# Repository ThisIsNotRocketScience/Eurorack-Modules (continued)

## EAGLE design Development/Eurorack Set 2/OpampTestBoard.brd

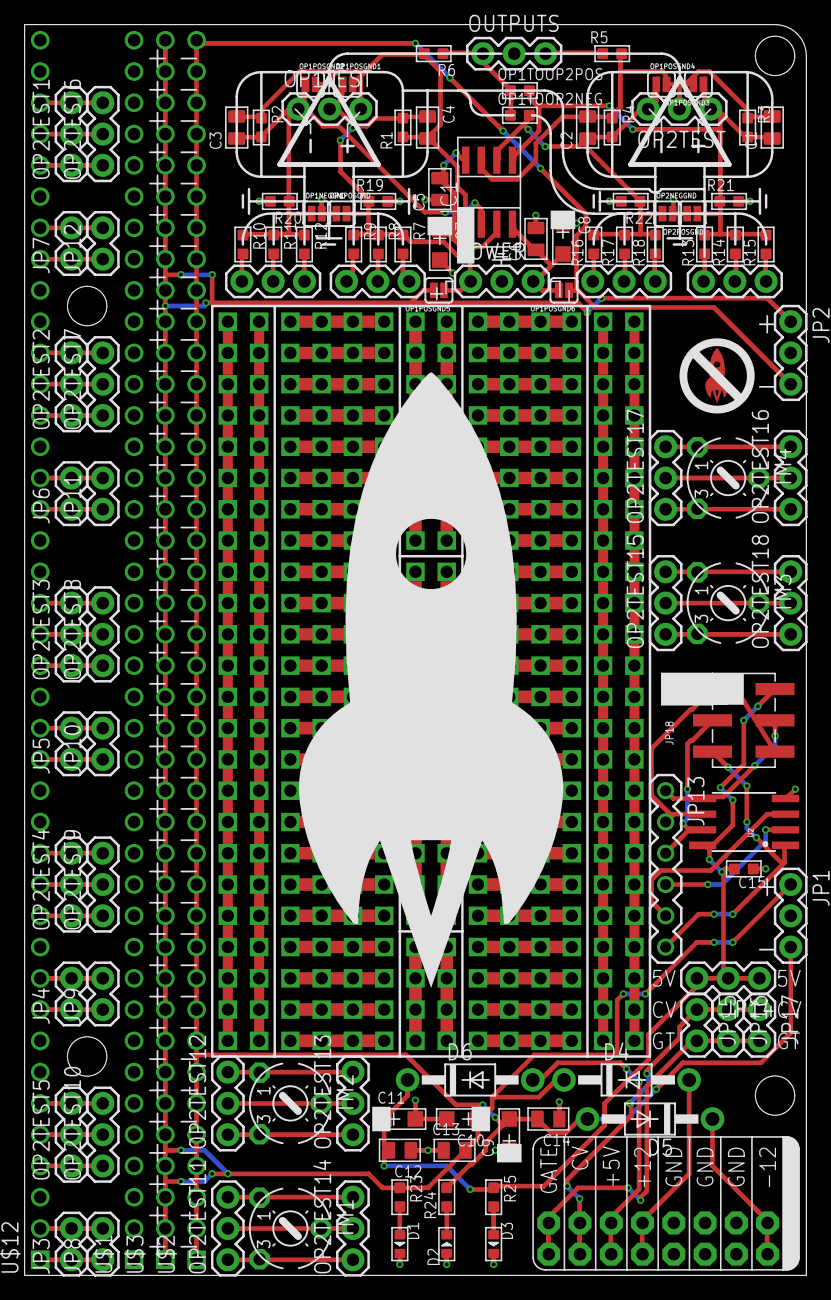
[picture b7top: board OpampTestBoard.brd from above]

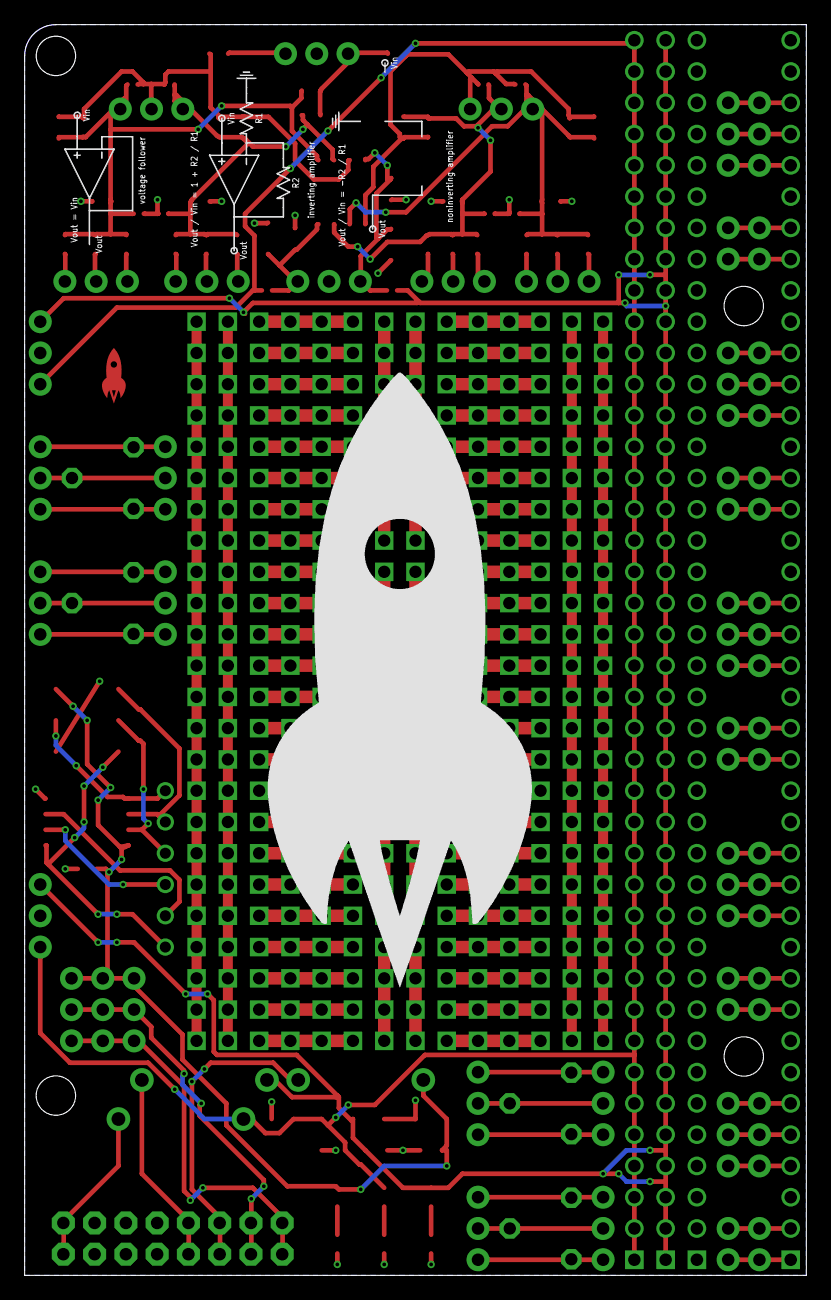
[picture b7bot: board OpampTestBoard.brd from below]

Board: 2 copper layers, 63.5 x 101.6 mm, 125 parts (5 on the bottom side), 77 nets.

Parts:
C1, C2, C3, C4, C5, C6, C12, C13, C14: C0805
C7, C8, C9, C10, C11: AVX-A
C15: C0603
D1, D2, D3: LED0603
D4, D5, D6: DO41-10
H1, H2, H3, H4: MOUNT-HOLE; 3.2-NOMARKINGS-SMALLSAFEZONE
IC1: TL072; SO08
JP1, JP2, JP14: 1X03
JP3, JP4, JP5, JP6, JP7, JP8, JP9, JP10, JP11, JP12, JP15, JP16, JP17: M02PTH; 1X02
JP13: 1X06
JP18: 2X3_SMT_POSTS
OP1NEG, OP1POS, OP1TEST, OP2NEG, OP2POS, OP2TEST, OP2TEST1, OP2TEST2, OP2TEST3, OP2TEST4, OP2TEST5, OP2TEST6, OP2TEST7, OP2TEST8, OP2TEST9, OP2TEST10, OP2TEST11, OP2TEST12, OP2TEST13, OP2TEST14, OP2TEST15, OP2TEST16, OP2TEST17, OP2TEST18: 1X03
OP1NEGGND, OP1POSGND, OP1POSGND1, OP1POSGND2, OP1POSGND3, OP1POSGND4, OP1POSGND5, OP1POSGND6, OP2NEGGND, OP2POSGND: SOLDERJUMPERNC; SJ_2S
OP1TOOP2NEG, OP1TOOP2POS: R0603
OUTPUTS: 1X03
POWER: 1X03
R1, R2, R3, R4, R5, R6, R7, R8, R9, R10, R11, R12, R13, R14, R15, R16, R17, R18, R19, R20, R21, R22, R23, R24, R25: R0603
TM1, TM2, TM3, TM4: 6MM
U2: Tiny85-20-SMT; SO08-EIAJ
U$1, U$2, U$3, U$12: M40; 1X40
U$4, U$7: SYMBOLSOPAMP; SYMB_OPAMP
U$5: R2; RESISTOR
U$6: R1; RESISTOR
U$8: SMALLROCKET
U$9: POWER; POWER_16
U$10, U$17: ROCKET-5CM
U$32: PROTOAREA; PROTO_10_24

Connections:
1: JP13.2, JP18.1, U2.6
2: JP13.3, JP18.3, U2.7
3: JP13.4, U2.2
4: JP13.5, U2.3
+5V: C11.+, C12.2, C15.2, D6.C, JP14.1, JP14.2, JP14.3, JP18.2, R25.1, U2.8
+12V: C10.+, C13.2, D4.C, JP1.1, JP2.1, OP1POSGND5.2, R23.1, U$3.1, U$3.2, U$3.3, U$3.4, U$3.5, U$3.6, U$3.7, U$3.8, U$3.9, U$3.10, U$3.11, U$3.12, U$3.13, U$3.14, U$3.15, U$3.16, U$3.17, U$3.18, U$3.19, U$3.20, U$3.21, U$3.22, U$3.23, U$3.24, U$3.25, U$3.26, U$3.27, U$3.28, U$3.29, U$3.30, U$3.31, U$3.32, U$3.33, U$3.34, U$3.35, U$3.36, U$3.37, U$3.38, U$3.39, U$3.40
-12V: C9.-, C14.2, D5.A, JP1.3, JP2.3, OP1POSGND6.1, R24.2, U$2.1, U$2.2, U$2.3, U$2.4, U$2.5, U$2.6, U$2.7, U$2.8, U$2.9, U$2.10, U$2.11, U$2.12, U$2.13, U$2.14, U$2.15, U$2.16, U$2.17, U$2.18, U$2.19, U$2.20, U$2.21, U$2.22, U$2.23, U$2.24, U$2.25, U$2.26, U$2.27, U$2.28, U$2.29, U$2.30, U$2.31, U$2.32, U$2.33, U$2.34, U$2.35, U$2.36, U$2.37, U$2.38, U$2.39, U$2.40
A1: OP2TEST1.3, OP2TEST6.3, U$12.38
A2: OP2TEST1.2, OP2TEST6.2, U$12.37
A3: OP2TEST1.1, OP2TEST6.1, U$12.36
B1: OP2TEST2.3, OP2TEST7.3, U$12.30
B2: OP2TEST2.2, OP2TEST7.2, U$12.29
B3: OP2TEST2.1, OP2TEST7.1, U$12.28
C1: OP2TEST3.3, OP2TEST8.3, U$12.22
C2: OP2TEST3.2, OP2TEST8.2, U$12.21
C3: OP2TEST3.1, OP2TEST8.1, U$12.20
CV: JP15.1, JP16.1, JP17.1, U$9.13, U$9.14
D1: OP2TEST4.3, OP2TEST9.3, U$12.14
D2: OP2TEST4.2, OP2TEST9.2, U$12.13
D3: OP2TEST4.1, OP2TEST9.1, U$12.12
E1: OP2TEST5.3, OP2TEST10.3, U$12.6
E2: OP2TEST5.2, OP2TEST10.2, U$12.5
E3: OP2TEST5.1, OP2TEST10.1, U$12.4
GATE: JP15.2, JP16.2, JP17.2, U$9.15, U$9.16
GND: C5.1, C6.2, C7.-, C8.+, C9.+, C10.-, C11.-, C12.1, C13.1, C14.1, C15.1, D1.-, D2.+, D3.-, JP1.2, JP2.2, JP18.6, OP1NEGGND.2, OP1POSGND.1, OP2NEGGND.2, OP2POSGND.2, OUTPUTS.2, POWER.2, R19.2, R20.2, R21.2, R22.2, U2.4, U$1.1, U$1.2, U$1.3, U$1.4, U$1.5, U$1.6, U$1.7, U$1.8, U$1.9, U$1.10, U$1.11, U$1.12, U$1.13, U$1.14, U$1.15, U$1.16, U$1.17, U$1.18, U$1.19, U$1.20, U$1.21, U$1.22, U$1.23, U$1.24, U$1.25, U$1.26, U$1.27, U$1.28, U$1.29, U$1.30, U$1.31, U$1.32, U$1.33, U$1.34, U$1.35, U$1.36, U$1.37, U$1.38, U$1.39, U$1.40, U$9.3, U$9.4, U$9.5, U$9.6, U$9.7, U$9.8, U$12.3, U$12.7, U$12.8, U$12.11, U$12.15, U$12.16, U$12.19, U$12.23, U$12.24, U$12.27, U$12.31, U$12.32, U$12.35, U$12.39, U$12.40
LA1: JP7.1, JP12.1, U$12.33
LA2: JP7.2, JP12.2, U$12.34
LB1: JP6.1, JP11.1, U$12.25
LB2: JP6.2, JP11.2, U$12.26
LC1: JP5.1, JP10.1, U$12.17
LC2: JP5.2, JP10.2, U$12.18
LD1: JP4.1, JP9.1, U$12.9
LD2: JP4.2, JP9.2, U$12.10
LE1: JP3.1, JP8.1, U$12.1
LE2: JP3.2, JP8.2, U$12.2
MOSI: JP13.1, JP18.4, U2.5
unnamed: OP1POS.3, R9.2
unnamed: OP1TOOP2NEG.1, OP1TOOP2POS.1, OUTPUTS.1, R6.1
unnamed: OP1POS.2, R8.2
unnamed: OUTPUTS.3, R5.1
unnamed: OP2TEST11.2, OP2TEST14.2, TM1.S
unnamed: OP2TEST12.2, OP2TEST13.2, TM2.S
unnamed: OP1POS.1, R7.2
unnamed: OP1NEG.3, R10.2
unnamed: OP1NEG.2, R11.2
unnamed: OP1NEG.1, R12.2
unnamed: OP2POS.3, R13.1
unnamed: OP2POS.2, R14.1
unnamed: OP2POS.1, R15.1
unnamed: OP2NEG.3, R16.1
unnamed: OP2NEG.2, R17.1
unnamed: OP2NEG.1, R18.1
unnamed: OP2TEST12.1, OP2TEST13.1, TM2.E
unnamed: D3.+, R25.2
unnamed: D1.+, R23.2
unnamed: D2.-, R24.1
unnamed: OP2TEST12.3, OP2TEST13.3, TM2.A
unnamed: OP2TEST11.1, OP2TEST14.1, TM1.E
unnamed: OP2TEST11.3, OP2TEST14.3, TM1.A
unnamed: OP2TEST15.2, OP2TEST18.2, TM3.S
unnamed: OP2TEST16.2, OP2TEST17.2, TM4.S
unnamed: OP2TEST16.1, OP2TEST17.1, TM4.E
unnamed: OP2TEST16.3, OP2TEST17.3, TM4.A
unnamed: OP2TEST15.1, OP2TEST18.1, TM3.E
unnamed: OP2TEST15.3, OP2TEST18.3, TM3.A
unnamed: D4.A, U$9.9, U$9.10
unnamed: D5.C, U$9.1, U$9.2
unnamed: D6.A, U$9.11, U$9.12
OP1NEG: C3.1, IC1.2, OP1NEGGND.1, OP1POSGND2.1, OP1TEST.1, R2.2, R10.1, R11.1, R12.1, R20.1
OP1OUT: C3.2, C4.2, IC1.1, OP1POSGND1.2, OP1POSGND2.2, OP1TEST.3, R1.1, R2.1, R6.2
OP1POS: C4.1, IC1.3, OP1POSGND.2, OP1POSGND1.1, OP1TEST.2, R1.2, R7.1, R8.1, R9.1, R19.1
OP2NEG: C2.1, IC1.6, OP1POSGND4.1, OP1TOOP2NEG.2, OP2NEGGND.1, OP2TEST.3, R4.2, R16.2, R17.2, R18.2, R22.1
OP2OUT: C1.2, C2.2, IC1.7, OP1POSGND3.2, OP1POSGND4.2, OP2TEST.2, R3.1, R4.1, R5.2
OP2POS: C1.1, IC1.5, OP1POSGND3.1, OP1TOOP2POS.2, OP2POSGND.1, OP2TEST.1, R3.2, R13.2, R14.2, R15.2, R21.1
RST: JP13.6, JP18.5, U2.1
VNEG: C6.1, C8.-, IC1.4, OP1POSGND6.2, POWER.3
VPOS: C5.2, C7.+, IC1.8, OP1POSGND5.1, POWER.1
